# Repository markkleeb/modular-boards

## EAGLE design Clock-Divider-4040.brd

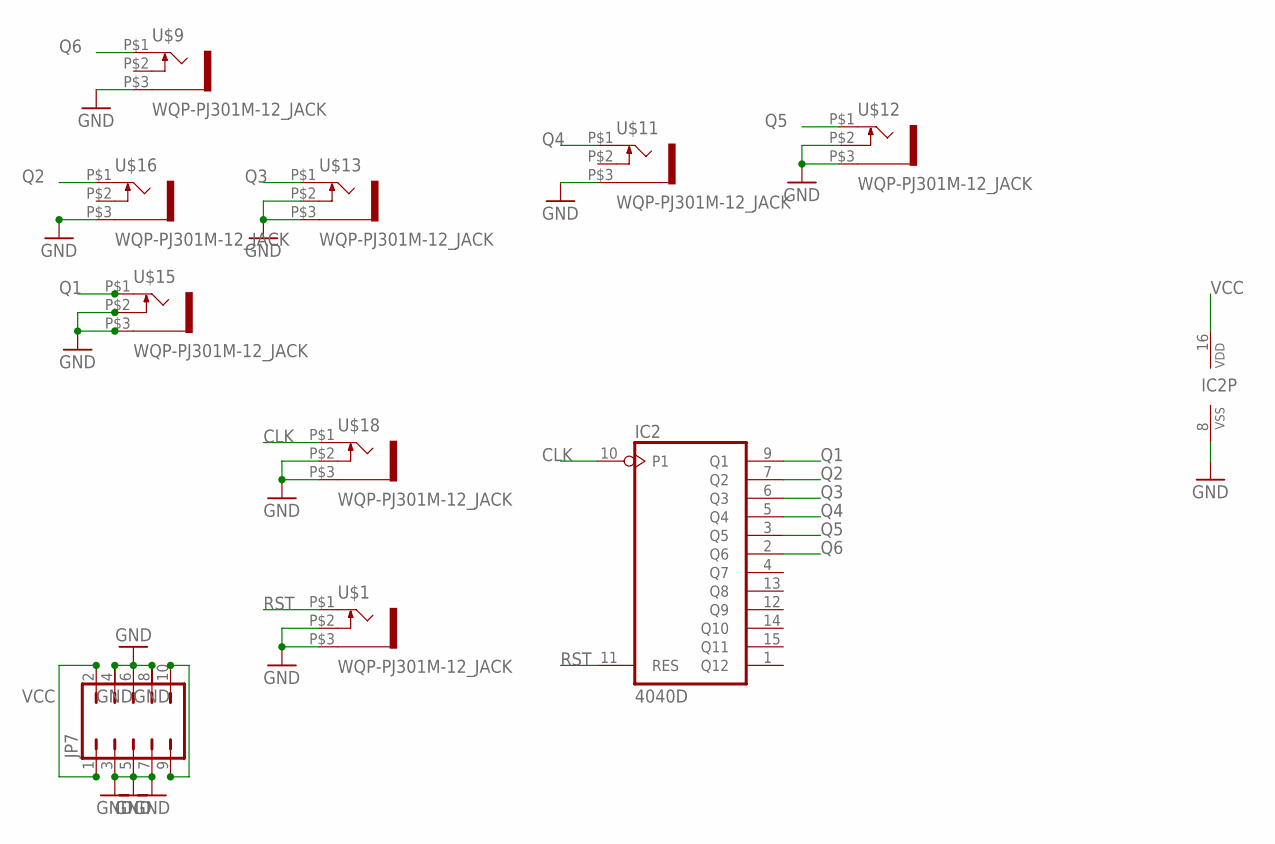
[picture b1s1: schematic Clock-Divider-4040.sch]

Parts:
IC2: 4040D; SO16
JP7: JP5Q
U$1, U$9, U$11, U$12, U$13, U$15, U$16, U$18: WQP-PJ301M-12_JACK

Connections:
CLK: IC2.10 (P1), U$18.P$1 (2)
GND: IC2.8 (VSS), JP7.3, JP7.4, JP7.5, JP7.6, JP7.7, JP7.8, U$1.P$2 (3), U$1.P$3 (1), U$9.P$3 (1), U$11.P$3 (1), U$12.P$2 (3), U$12.P$3 (1), U$13.P$2 (3), U$13.P$3 (1), U$15.P$2 (3), U$15.P$3 (1), U$16.P$3 (1), U$18.P$2 (3), U$18.P$3 (1)
unnamed: JP7.9, JP7.10
Q1: IC2.9 (Q1), U$15.P$1 (2)
Q2: IC2.7 (Q2), U$16.P$1 (2)
Q3: IC2.6 (Q3), U$13.P$1 (2)
Q4: IC2.5 (Q4), U$11.P$1 (2)
Q5: IC2.3 (Q5), U$12.P$1 (2)
Q6: IC2.2 (Q6), U$9.P$1 (2)
RST: IC2.11 (RES), U$1.P$1 (2)
VCC: IC2.16 (VDD), JP7.1, JP7.2

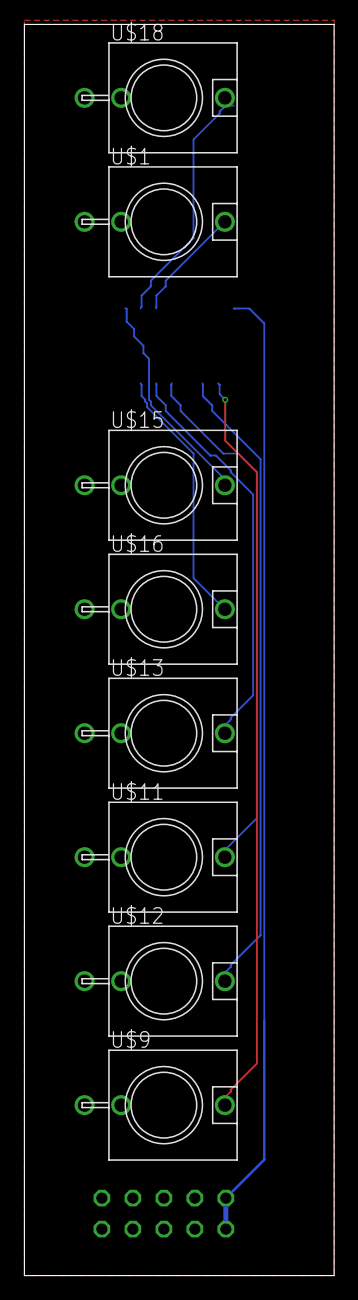
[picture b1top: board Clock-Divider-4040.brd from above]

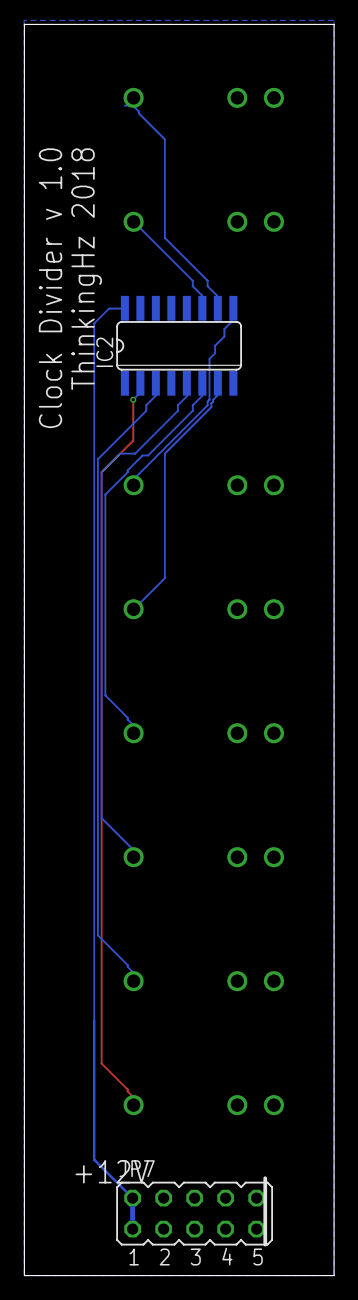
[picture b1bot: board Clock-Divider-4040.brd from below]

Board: 2 copper layers, 25.4 x 102.5 mm, 10 parts (2 on the bottom side), 11 nets.

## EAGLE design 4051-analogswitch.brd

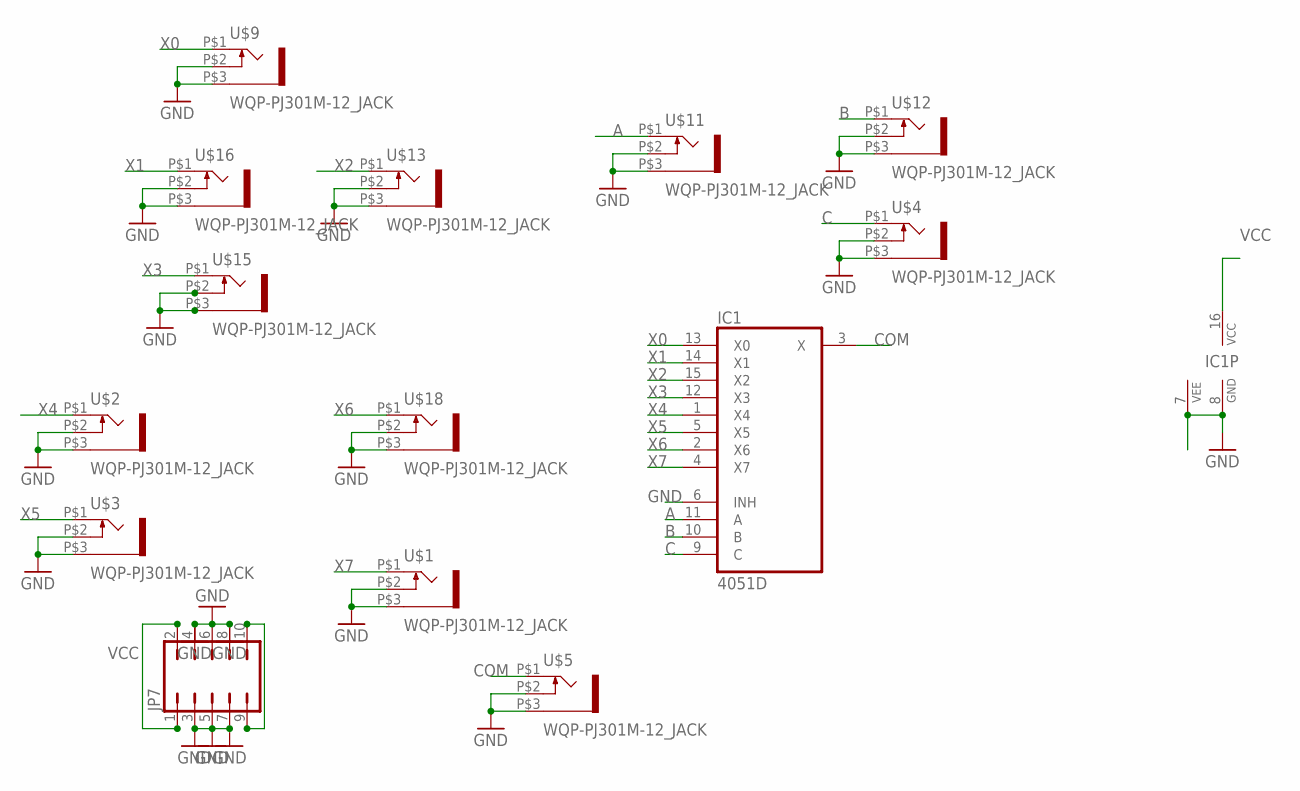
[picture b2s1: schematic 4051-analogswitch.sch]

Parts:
IC1: 4051D; SO16
JP7: JP5Q
U$1, U$2, U$3, U$4, U$5, U$9, U$11, U$12, U$13, U$15, U$16, U$18: WQP-PJ301M-12_JACK

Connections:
A: IC1.11 (A), U$11.P$1 (2)
B: IC1.10 (B), U$12.P$1 (2)
C: IC1.9 (C), U$4.P$1 (2)
COM: IC1.3 (X), U$5.P$1 (2)
GND: IC1.6 (INH), IC1.7 (VEE), IC1.8 (GND), JP7.3, JP7.4, JP7.5, JP7.6, JP7.7, JP7.8, U$1.P$2 (3), U$1.P$3 (1), U$2.P$2 (3), U$2.P$3 (1), U$3.P$2 (3), U$3.P$3 (1), U$4.P$2 (3), U$4.P$3 (1), U$5.P$2 (3), U$5.P$3 (1), U$9.P$2 (3), U$9.P$3 (1), U$11.P$2 (3), U$11.P$3 (1), U$12.P$2 (3), U$12.P$3 (1), U$13.P$2 (3), U$13.P$3 (1), U$15.P$2 (3), U$15.P$3 (1), U$16.P$2 (3), U$16.P$3 (1), U$18.P$2 (3), U$18.P$3 (1)
unnamed: JP7.9, JP7.10
VCC: IC1.16 (VCC), JP7.1, JP7.2
X0: IC1.13 (X0), U$9.P$1 (2)
X1: IC1.14 (X1), U$16.P$1 (2)
X2: IC1.15 (X2), U$13.P$1 (2)
X3: IC1.12 (X3), U$15.P$1 (2)
X4: IC1.1 (X4), U$2.P$1 (2)
X5: IC1.5 (X5), U$3.P$1 (2)
X6: IC1.2 (X6), U$18.P$1 (2)
X7: IC1.4 (X7), U$1.P$1 (2)

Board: 2 copper layers, 14 parts (2 on the bottom side), 15 nets, no tracks yet.

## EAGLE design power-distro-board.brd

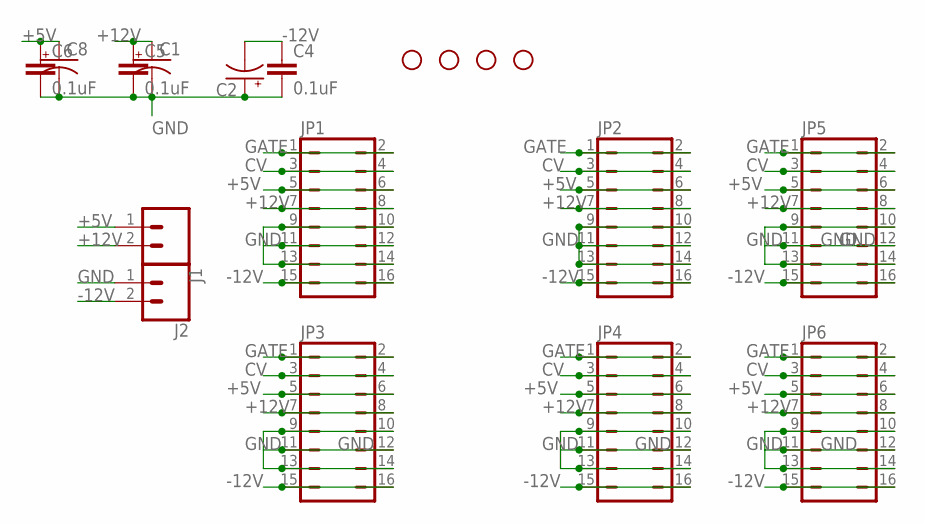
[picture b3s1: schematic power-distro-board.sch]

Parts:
C1, C2, C8: CPOL-USE2.5-6; E2,5-6
C4, C5, C6: 0.1uF; CAP-PTH-SMALL-KIT
H1, H2, H3, H4: STAND-OFF
J1, J2: CONN_023.5MM; SCREWTERMINAL-3.5MM-2
JP1, JP2, JP3, JP4, JP5, JP6: JP8Q

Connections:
+5V: C6.1, C8.+, J1.1, JP1.5, JP1.6, JP2.5, JP2.6, JP3.5, JP3.6, JP4.5, JP4.6, JP5.5, JP5.6, JP6.5, JP6.6
+12V: C1.+, C5.1, J1.2, JP1.7, JP1.8, JP2.7, JP2.8, JP3.7, JP3.8, JP4.7, JP4.8, JP5.7, JP5.8, JP6.7, JP6.8
-12V: C2.-, C4.1, J2.2, JP1.15, JP1.16, JP2.15, JP2.16, JP3.15, JP3.16, JP4.15, JP4.16, JP5.15, JP5.16, JP6.15, JP6.16
CV: JP1.3, JP1.4, JP2.3, JP2.4, JP3.3, JP3.4, JP4.3, JP4.4, JP5.3, JP5.4, JP6.3, JP6.4
GATE: JP1.1, JP1.2, JP2.1, JP2.2, JP3.1, JP3.2, JP4.1, JP4.2, JP5.1, JP5.2, JP6.1, JP6.2
GND: C1.-, C2.+, C4.2, C5.2, C6.2, C8.-, J2.1, JP1.9, JP1.10, JP1.11, JP1.12, JP1.13, JP1.14, JP2.9, JP2.10, JP2.11, JP2.12, JP2.13, JP2.14, JP3.9, JP3.10, JP3.11, JP3.12, JP3.13, JP3.14, JP4.9, JP4.10, JP4.11, JP4.12, JP4.13, JP4.14, JP5.9, JP5.10, JP5.11, JP5.12, JP5.13, JP5.14, JP6.9, JP6.10, JP6.11, JP6.12, JP6.13, JP6.14

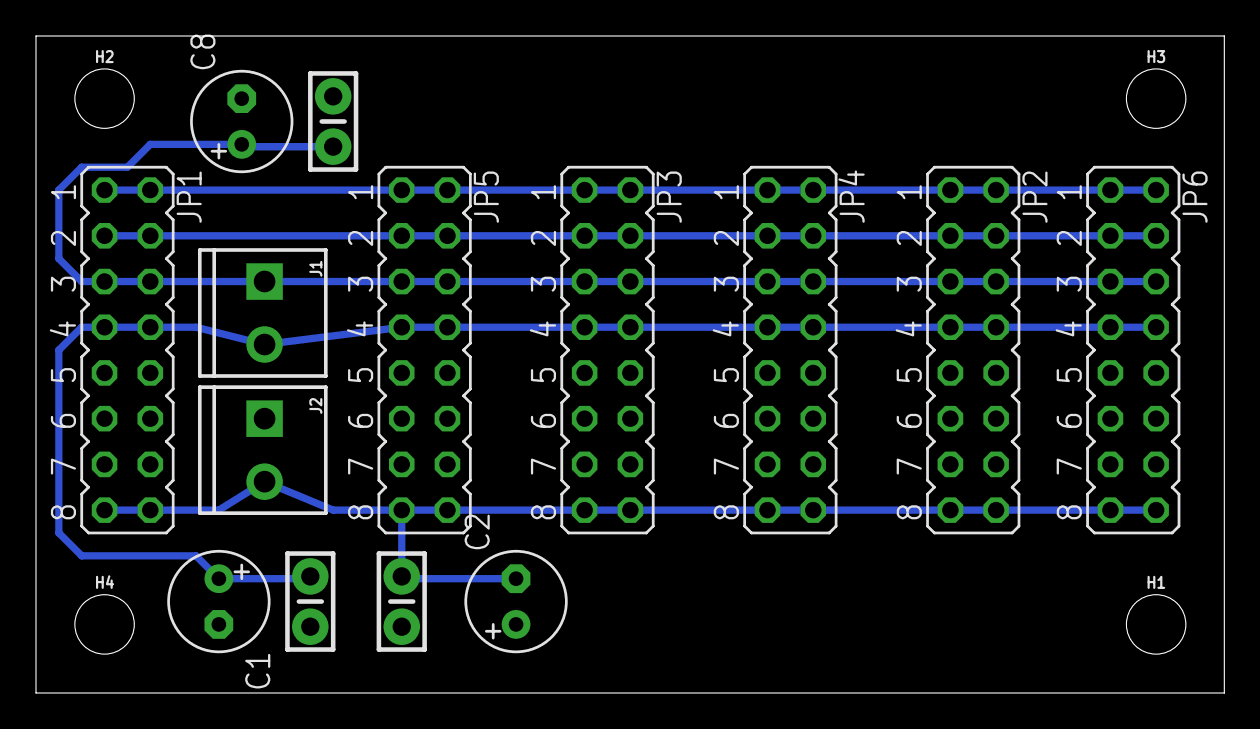
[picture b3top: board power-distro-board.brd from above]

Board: 2 copper layers, 66.0 x 36.5 mm, 18 parts (0 on the bottom side), 6 nets.

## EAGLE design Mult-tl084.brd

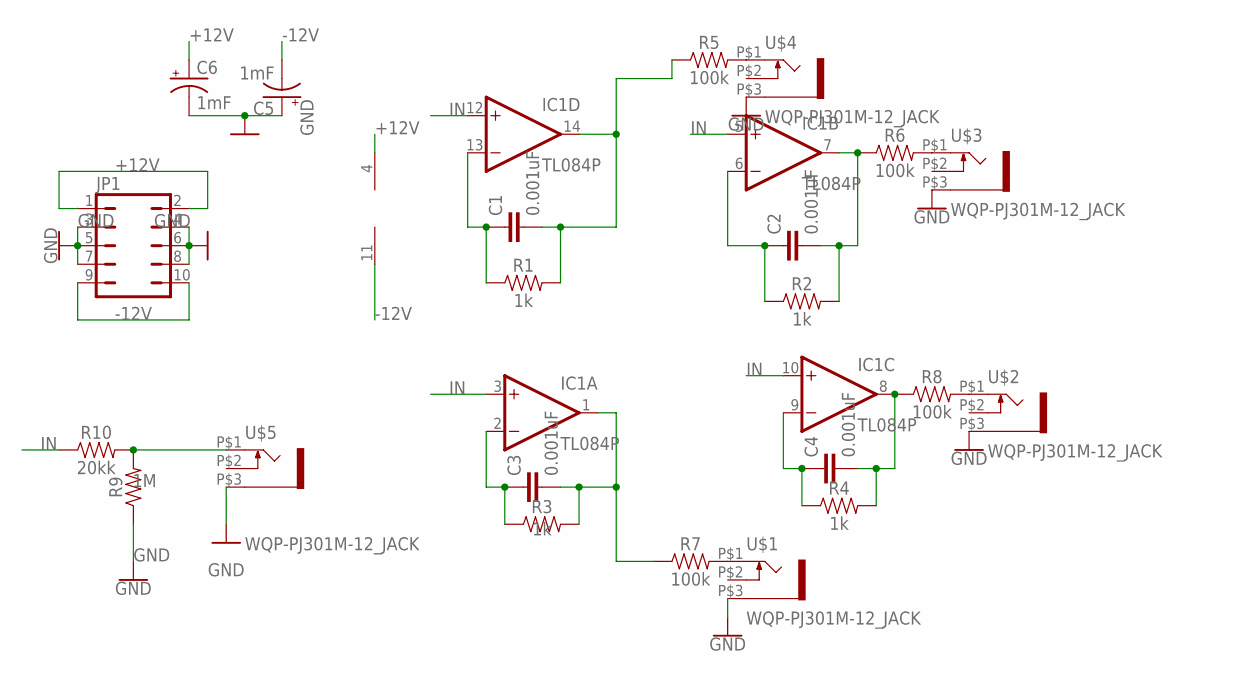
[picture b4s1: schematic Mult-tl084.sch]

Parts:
C1, C2, C3, C4: 0.001uF; CAP-PTH-SMALL-KIT
C5, C6: 1mF; CPOL-RADIAL-5MM-10MM
IC1: TL084P; DIL14
JP1: JP5Q
R1, R2, R3, R4: 1k; AXIAL-0.3
R5, R6, R7, R8: 100k; AXIAL-0.3
R9: 1M; AXIAL-0.3
R10: 20kk; AXIAL-0.3
U$1, U$2, U$3, U$4, U$5: WQP-PJ301M-12_JACK

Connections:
+12V: C6.+, IC1.4 (V+), JP1.1, JP1.2
-12V: C5.-, IC1.11 (V-), JP1.9, JP1.10
GND: C5.+, C6.-, JP1.3, JP1.4, JP1.5, JP1.6, JP1.7, JP1.8, R9.P$1 (1), U$1.P$3 (1), U$2.P$3 (1), U$3.P$3 (1), U$4.P$3 (1), U$5.P$3 (1)
IN: IC1.3 (+IN), IC1.5 (+IN), IC1.10 (+IN), IC1.12 (+IN), R10.P$1 (1)
unnamed: C1.1, IC1.13 (-IN), R1.P$1 (1)
unnamed: C1.2, IC1.14 (OUT), R1.P$2 (2), R5.P$1 (1)
unnamed: C2.1, IC1.6 (-IN), R2.P$1 (1)
unnamed: C2.2, IC1.7 (OUT), R2.P$2 (2), R6.P$1 (1)
unnamed: C3.1, IC1.2 (-IN), R3.P$1 (1)
unnamed: C3.2, IC1.1 (OUT), R3.P$2 (2), R7.P$1 (1)
unnamed: C4.1, IC1.9 (-IN), R4.P$1 (1)
unnamed: R8.P$2 (2), U$2.P$1 (2)
unnamed: C4.2, IC1.8 (OUT), R4.P$2 (2), R8.P$1 (1)
unnamed: R6.P$2 (2), U$3.P$1 (2)
unnamed: R5.P$2 (2), U$4.P$1 (2)
unnamed: R7.P$2 (2), U$1.P$1 (2)
unnamed: R9.P$2 (2), R10.P$2 (2), U$5.P$1 (2)

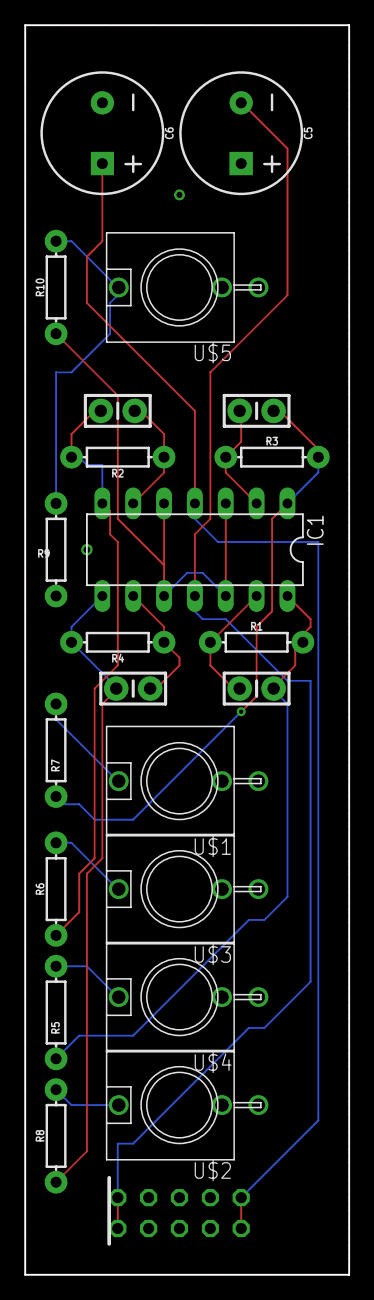
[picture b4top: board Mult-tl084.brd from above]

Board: 2 copper layers, 26.7 x 102.9 mm, 23 parts (1 on the bottom side), 17 nets.

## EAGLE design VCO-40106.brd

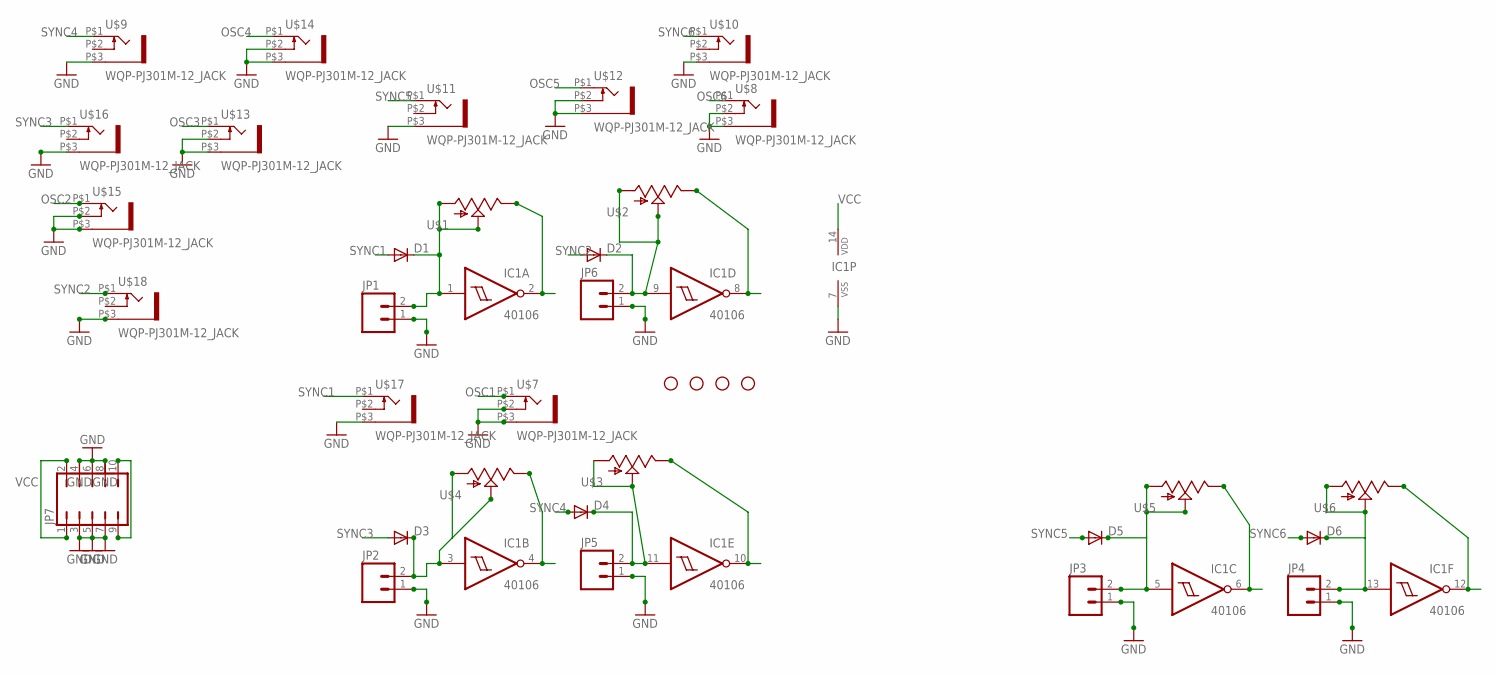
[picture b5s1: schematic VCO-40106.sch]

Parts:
D1, D2, D3, D4, D5, D6: DIODE1N4148; DIODE-1N4148
IC1: 40106; DIL14
JP1, JP2, JP3, JP4, JP5, JP6: M02; 1X02_LONGPADS
JP7: JP5Q
JP8, JP9, JP10, JP11: STAND-OFF
U$1, U$2, U$3, U$4, U$5, U$6: POT; ALPS_POT
U$7, U$8, U$9, U$10, U$11, U$12, U$13, U$14, U$15, U$16, U$17, U$18: WQP-PJ301M-12_JACK

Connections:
GND: IC1.7 (VSS), JP1.1, JP2.1, JP3.1, JP4.1, JP5.1, JP6.1, JP7.3, JP7.4, JP7.5, JP7.6, JP7.7, JP7.8, U$7.P$2 (3), U$7.P$3 (1), U$8.P$2 (3), U$8.P$3 (1), U$9.P$3 (1), U$10.P$3 (1), U$11.P$3 (1), U$12.P$2 (3), U$12.P$3 (1), U$13.P$2 (3), U$13.P$3 (1), U$14.P$2 (3), U$14.P$3 (1), U$15.P$2 (3), U$15.P$3 (1), U$16.P$3 (1), U$17.P$3 (1), U$18.P$3 (1)
unnamed: D1.C, IC1.1 (I), JP1.2, U$1.P$2 (S), U$1.P$3 (A)
unnamed: D3.C, IC1.3 (I), JP2.2, U$4.P$2 (S), U$4.P$3 (A)
unnamed: D5.C, IC1.5 (I), JP3.2, U$5.P$2 (S), U$5.P$3 (A)
unnamed: JP7.9, JP7.10
unnamed: D2.C, IC1.9 (I), JP6.2, U$2.P$2 (S), U$2.P$3 (A)
unnamed: D4.C, IC1.11 (I), JP5.2, U$3.P$2 (S), U$3.P$3 (A)
unnamed: D6.C, IC1.13 (I), JP4.2, U$6.P$2 (S), U$6.P$3 (A)
OSC1: IC1.2 (O), U$1.P$1 (E), U$7.P$1 (2)
OSC2: IC1.4 (O), U$4.P$1 (E), U$15.P$1 (2)
OSC3: IC1.6 (O), U$5.P$1 (E), U$13.P$1 (2)
OSC4: IC1.8 (O), U$2.P$1 (E), U$14.P$1 (2)
OSC5: IC1.10 (O), U$3.P$1 (E), U$12.P$1 (2)
OSC6: IC1.12 (O), U$6.P$1 (E), U$8.P$1 (2)
SYNC1: D1.A, U$17.P$1 (2)
SYNC2: D2.A, U$18.P$1 (2)
SYNC3: D3.A, U$16.P$1 (2)
SYNC4: D4.A, U$9.P$1 (2)
SYNC5: D5.A, U$11.P$1 (2)
SYNC6: D6.A, U$10.P$1 (2)
VCC: IC1.14 (VDD), JP7.1, JP7.2

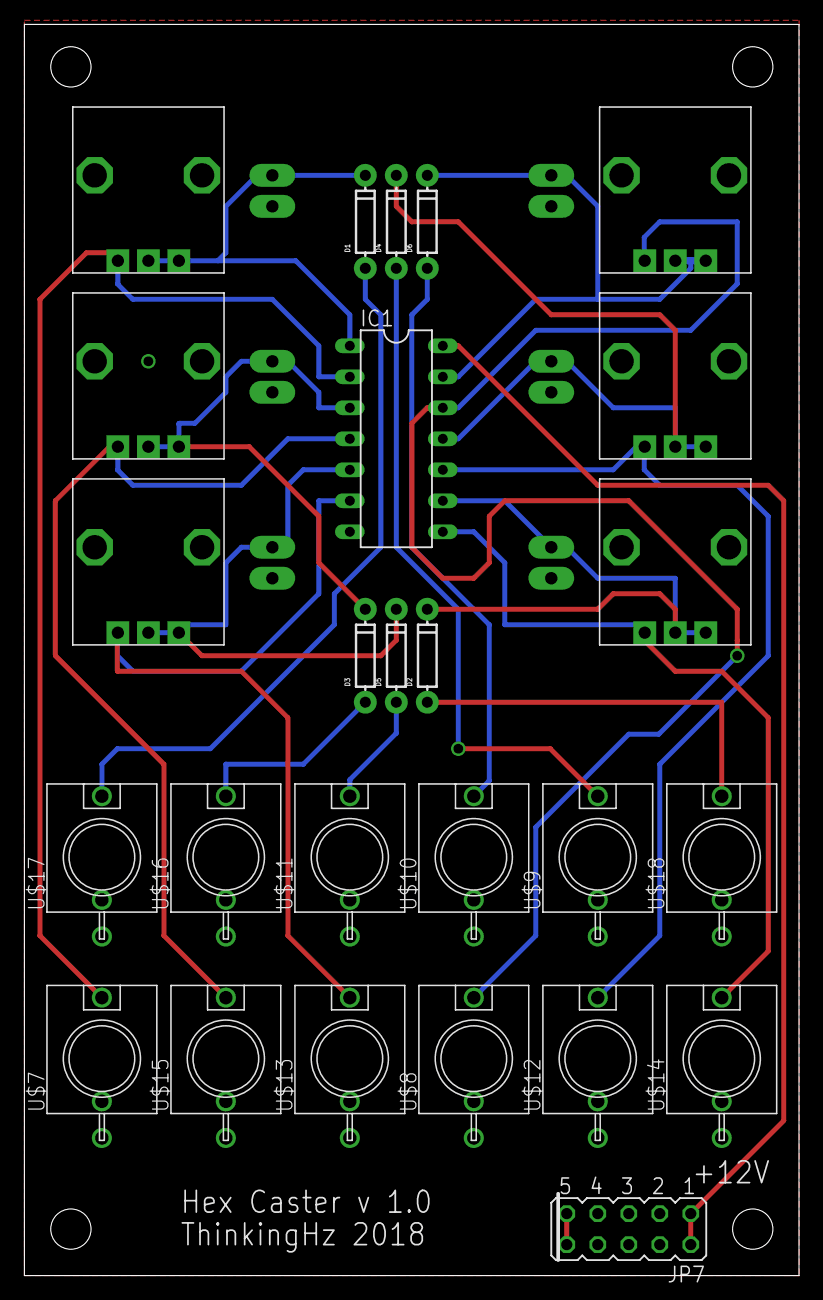
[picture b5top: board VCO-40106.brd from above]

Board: 2 copper layers, 63.5 x 102.5 mm, 36 parts (0 on the bottom side), 21 nets.

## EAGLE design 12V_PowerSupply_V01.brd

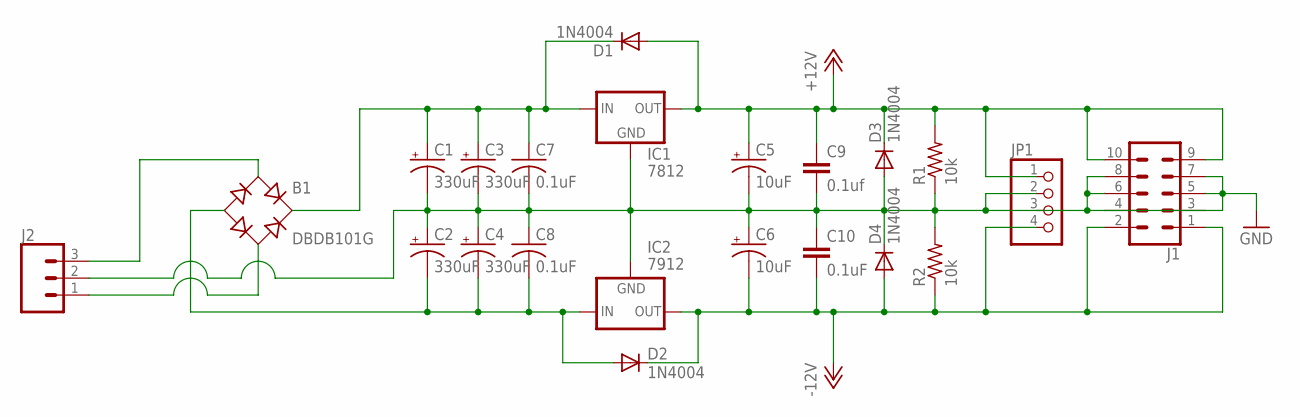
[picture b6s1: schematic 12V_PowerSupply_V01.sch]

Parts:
B1: DBDB101G; DB
C1, C2, C3, C4: 330uF; E7,5-18
C5, C6: 10uF; E2,5-7
C7, C8: 0.1uF; C150-054X183
C9: 0.1uf; C050-025X075
C10: 0.1uF; C050-025X075
D1, D2, D3, D4: 1N4004; DO41-10
IC1: 7812; 78XXS
IC2: 7912; 79XXS
J1: CONN_05X2SHD; 2X5-SHROUDED
J2: CONN_03-SCREW-5MM; SCREWTERMINAL-5MM-3
JP1: PINHD-1X4; 1X04
R1, R2: 10k; 0204/7

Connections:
+12V: C5.+, C9.1, D1.A, D3.C, IC1.OUT, J1.9, J1.10, JP1.1, R1.2
-12V: C6.-, C10.2, D2.C, D4.A, IC2.OUT, J1.1, J1.2, JP1.4, R2.1
GND: C1.-, C2.+, C3.-, C4.+, C5.-, C6.+, C7.2, C8.1, C9.2, C10.1, D3.A, D4.C, IC1.GND, IC2.GND, J1.3, J1.4, J1.5, J1.6, J1.7, J1.8, J2.2, JP1.2, JP1.3, R1.1, R2.2
unnamed: B1.+, C1.+, C3.+, C7.1, D1.C, IC1.IN
unnamed: B1.-, C2.-, C4.-, C8.2, D2.A, IC2.IN
unnamed: B1.AC1, J2.3
unnamed: B1.AC2, J2.1

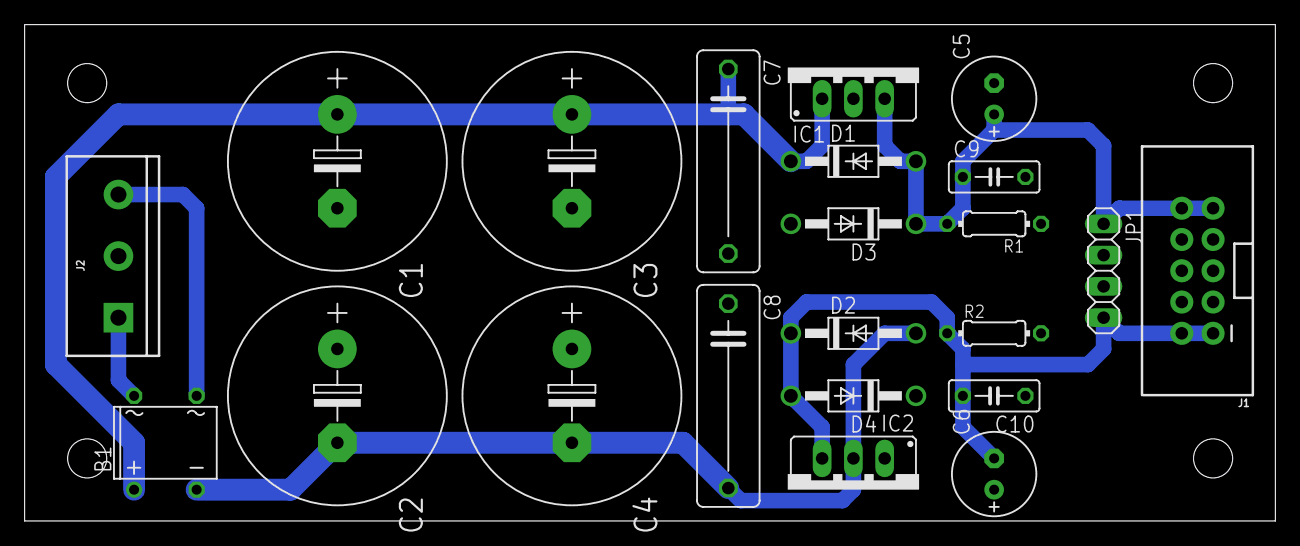
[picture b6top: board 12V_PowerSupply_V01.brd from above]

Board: 2 copper layers, 101.6 x 40.3 mm, 22 parts (0 on the bottom side), 7 nets.

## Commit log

2018-12-31 Illustrator Files

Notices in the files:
parts and their libraries:
SparkFun-Connectors: Licensing: Creative Commons ShareAlike 4.0 International - https://creativecommons.org/licenses/by-sa/4.0
